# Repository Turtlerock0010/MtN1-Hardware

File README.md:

# MtN1-Hardware

> MtN1 Draft 1 3D Model, WIP

> [!IMPORTANT]
> [Check discussions and help out!!! 🥹](https://github.com/Turtlerock0010/MtN1-Hardware/discussions)

> [!NOTE]
> This is the hardware repository for the MtN1! For MtN1 software, go to [MtN1-Lib](https://github.com/Turtlerock0010/MtN1-Lib).

## About

### Q: What is this project?
A: The MtN1 (Motion-1) is a robotics motion expansion board designed to work with any microcontroller that supports QWIIC or I2C!

### Q: What is the goal of this project?
A: The goal of the MtN1 is to ensure complexity is a choice, not a compromise. Although simplicity and constraints allow for mechanisms that are designed with robustness, MtN1 is designed to allow for seasoned and rookie roboticists to truly expand on individual STEM efficacy.

### Q: What was the inspiration for this board?
A: Within MiniFRC -- an event hosted by The Terrorbytes [4561] -- I saw many very impressive creations, ranging from complete swerve drivetrains to advanced vision systems. But one common thread between them were the compromises made in order to work within the bounds of the most common robotics board used. Even I and the MiniFRC team I'm in (The Pink Fluffy Unicorns [83]) deliberated on how to distribute or simplify systems to fit these physical bounds!

### Q: Wait, no microcontroller onboard?
A: Yes!!! The MtN1 does not use a microcontroller. Instead, it uses a distributed control architecture to act as a primative version of one. This allows for cheaper costs, low latency control, universal I2C compatability, and 2 GPIO pin control!

### Q: Why the name MtN1 (Motion-1)?
A: I chose the name MtN1 as I felt like it was the name that properly describes the board's capabilities; and it looks stylish 😎.

## Non-Final Schematic

> MtN1 Draft 1 Schematic, WIP

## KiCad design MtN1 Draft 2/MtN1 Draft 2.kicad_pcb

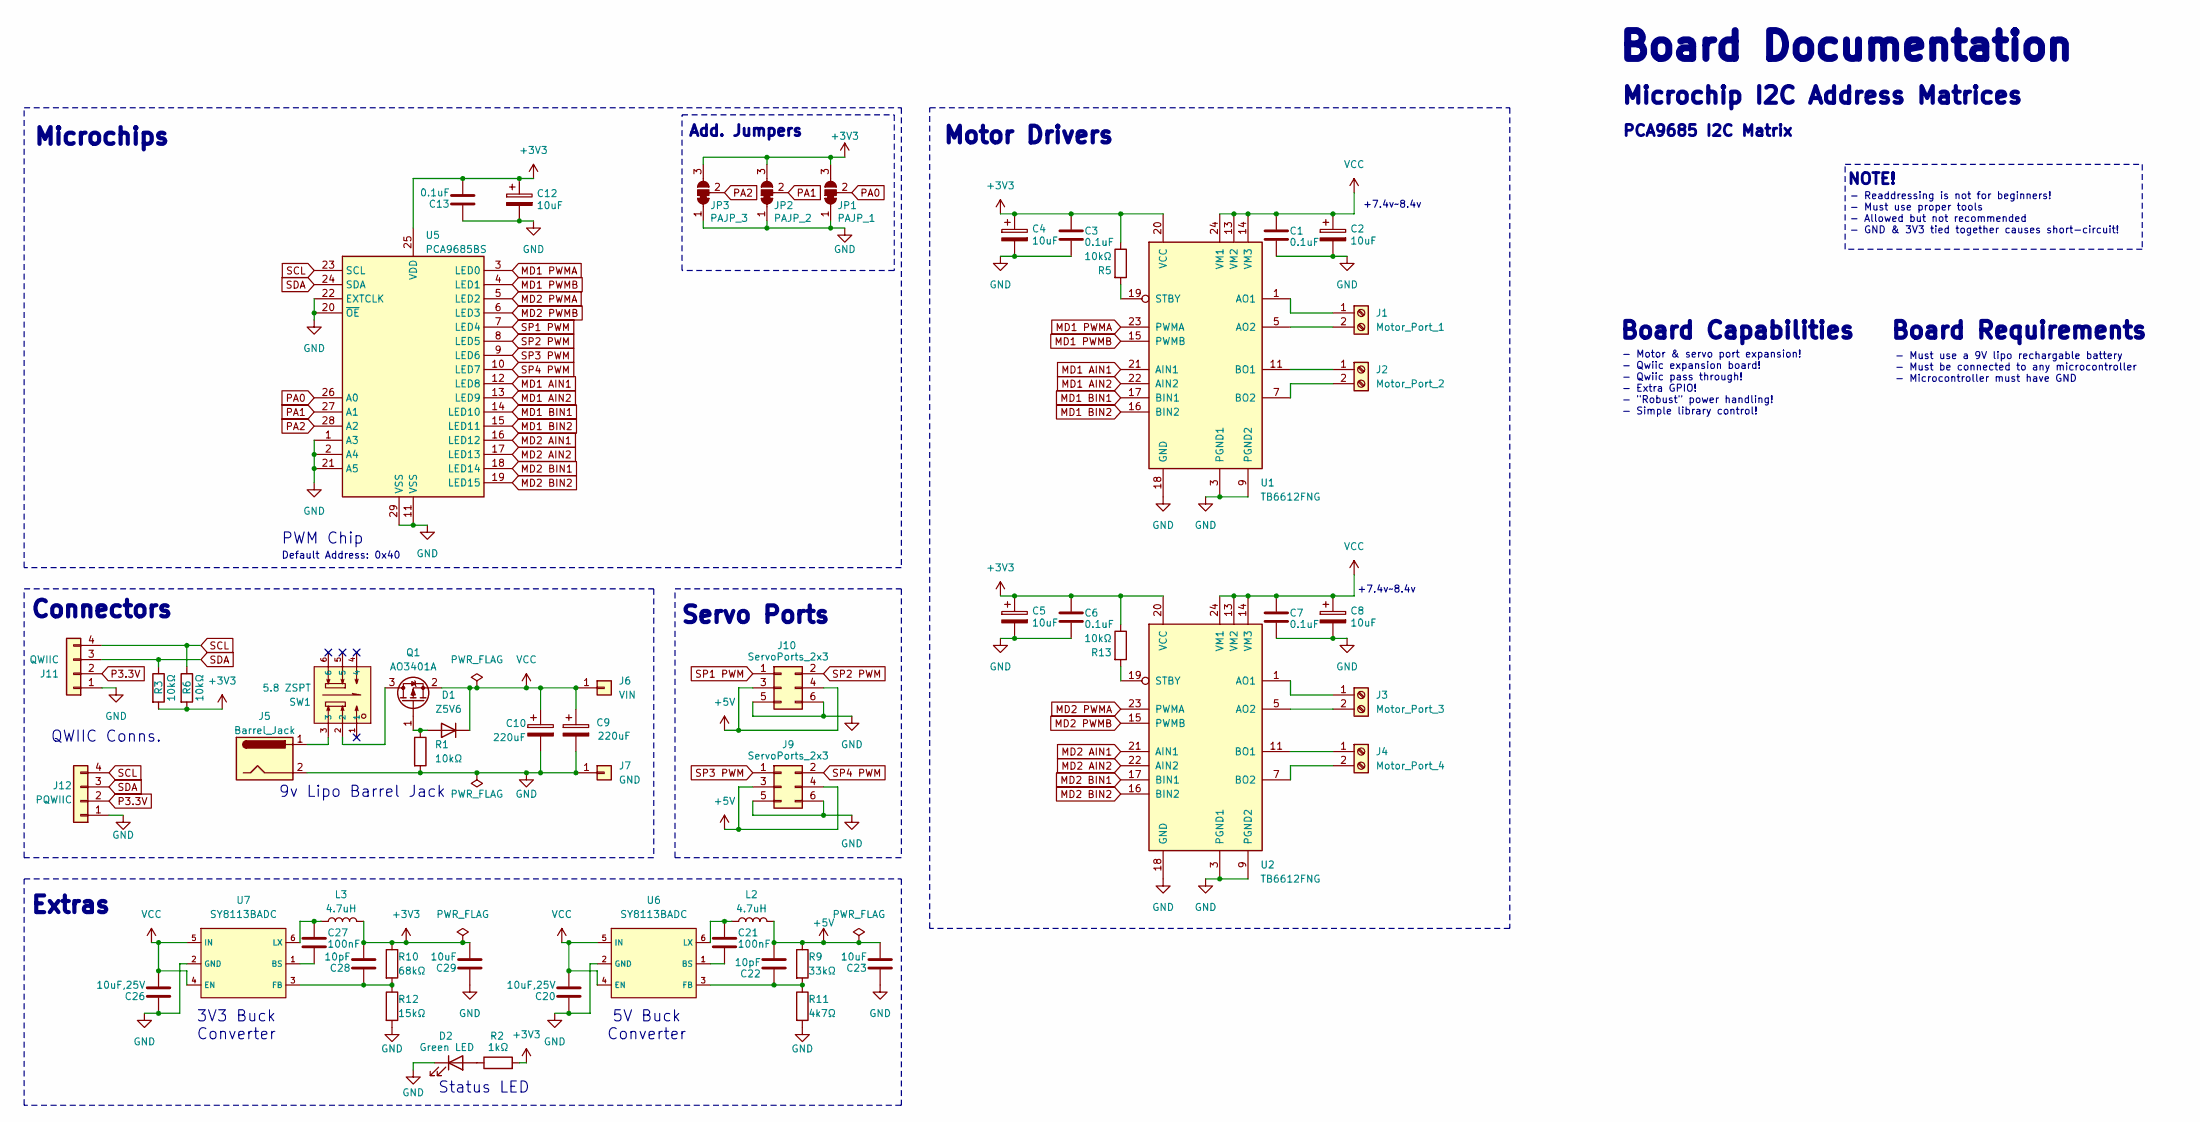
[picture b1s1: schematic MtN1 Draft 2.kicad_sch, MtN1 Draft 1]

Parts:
C1, C3, C6, C7, C13: 0.1uF; C_0402
C2, C4, C5, C8, C12: 10uF; C_0402
C9, C10: 220uF; CP_Elec_6.3x7.7
C20, C26: 10uF,25V; C_0603
C21, C27: 100nF; C_0402
C22, C28: 10pF; C_0402
C23, C29: 10uF; C_0603
D1: Z5V6; D_SOD-123
D2: Green LED; LED_0603_1608Metric
J1: Motor_Port_1; C8404_CONN-TH_WJ126V-5_0-2P
J2: Motor_Port_2; C8404_CONN-TH_WJ126V-5_0-2P
J3: Motor_Port_3; C8404_CONN-TH_WJ126V-5_0-2P
J4: Motor_Port_4; C8404_CONN-TH_WJ126V-5_0-2P
J5: Barrel_Jack; BarrelJack_Horizontal
J6: VIN; TestPoint_Pad_2.0x2.0mm
J7: GND; TestPoint_Pad_2.0x2.0mm
J9, J10: ServoPorts_2x3; PinHeader_2x03_P2.54mm_Vertical
J11: QWIIC; JST_SH_BM04B-SRSS-TB_1x04-1MP_P1.00mm_Vertical
J12: PQWIIC; JST_SH_BM04B-SRSS-TB_1x04-1MP_P1.00mm_Vertical
JP1: PAJP_1; SolderJumper-3_P1.3mm_Bridged12_RoundedPad1.0x1.5mm
JP2: PAJP_2; SolderJumper-3_P1.3mm_Bridged12_RoundedPad1.0x1.5mm
JP3: PAJP_3; SolderJumper-3_P1.3mm_Bridged12_RoundedPad1.0x1.5mm
L2, L3: 4.7uH; C98354_IND-SMD_L2_5-W2_0_WPN252012H
Q1: AO3401A; SOT-23
R1: 10kΩ; R_0603
R2: 1kΩ; R_0402
R3, R5, R6: 10kΩ; R_0402
R9: 33kΩ; R_0402
R10: 68kΩ; R_0402
R11: 4k7Ω; R_0402
R12: 15kΩ; R_0402
R13: 10kΩ; C25744_R0402
SW1: 5.8 ZSPT; C2681588_SW-TH_5_8ZSPT; LCSC C2681588
U1, U2: TB6612FNG; SSOP-24_5.3x8.2mm_P0.65mm
U5: PCA9685BS; QFN-28-1EP_6x6mm_P0.65mm_EP4.25x4.25mm
U6, U7: SY8113BADC; C78989_TSOT-23-6_L2_9-W1_6-P0_95-LS2_8-BR; LCSC C78989

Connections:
+3V3: C3.1, C4.1, C5.1, C6.1, C12.1, C13.2, C28.2, C29.2, JP1.3 (B), JP2.3 (B), JP3.3 (B), L3.2, R2.2, R3.2, R5.1, R6.2, R10.1, R13.1, U1.20 (VCC), U2.20 (VCC), U5.25 (VDD)
+5V: C22.2, C23.2, J9.3, J9.4, J10.3, J10.4, L2.2, R9.1
GND: C1.2, C2.2, C3.2, C4.2, C5.2, C6.2, C7.2, C8.2, C9.2, C10.2, C12.2, C13.1, C20.1, C23.1, C26.1, C29.1, D2.1 (K), J5.2, J7.1 (Pin_1_1), J9.5, J9.6, J10.5, J10.6, J11.1, J12.1, JP1.1 (A), JP2.1 (A), JP3.1 (A), R1.2, R11.2, R12.2, U1.3 (PGND1), U1.4 (PGND1), U1.9 (PGND2), U1.10 (PGND2), U1.18 (GND), U2.3 (PGND1), U2.4 (PGND1), U2.9 (PGND2), U2.10 (PGND2), U2.18 (GND), U5.1 (A3), U5.2 (A4), U5.11 (VSS), U5.20 (~OE), U5.21 (A5), U5.22 (EXTCLK), U5.29 (VSS), U6.2 (GND), U7.2 (GND)
MD1 AIN1: U1.21 (AIN1), U5.12 (LED8)
MD1 AIN2: U1.22 (AIN2), U5.13 (LED9)
MD1 BIN1: U1.17 (BIN1), U5.14 (LED10)
MD1 BIN2: U1.16 (BIN2), U5.15 (LED11)
MD1 PWMA: U1.23 (PWMA), U5.3 (LED0)
MD1 PWMB: U1.15 (PWMB), U5.4 (LED1)
MD2 AIN1: U2.21 (AIN1), U5.16 (LED12)
MD2 AIN2: U2.22 (AIN2), U5.17 (LED13)
MD2 BIN1: U2.17 (BIN1), U5.18 (LED14)
MD2 BIN2: U2.16 (BIN2), U5.19 (LED15)
MD2 PWMA: U2.23 (PWMA), U5.5 (LED2)
MD2 PWMB: U2.15 (PWMB), U5.6 (LED3)
unnamed: D1.2 (A), Q1.1 (G), R1.1
unnamed: D2.2 (A), R2.1
unnamed: J1.1, U1.1 (AO1), U1.2 (AO1)
unnamed: J1.2, U1.5 (AO2), U1.6 (AO2)
unnamed: J2.1, U1.11 (BO1), U1.12 (BO1)
unnamed: J2.2, U1.7 (BO2), U1.8 (BO2)
unnamed: J3.1, U2.1 (AO1), U2.2 (AO1)
unnamed: J3.2, U2.5 (AO2), U2.6 (AO2)
unnamed: J4.1, U2.11 (BO1), U2.12 (BO1)
unnamed: J4.2, U2.7 (BO2), U2.8 (BO2)
unnamed: J5.1, SW1.3
unnamed: Q1.3 (D), SW1.2
unnamed: R5.2, U1.19 (STBY)
unnamed: R13.2, U2.19 (STBY)
unnamed: C21.1, U6.1 (BS)
unnamed: C22.1, R9.2, R11.1, U6.3 (FB)
unnamed: C21.2, L2.1, U6.6 (LX)
unnamed: C27.1, U7.1 (BS)
unnamed: C28.1, R10.2, R12.1, U7.3 (FB)
unnamed: C27.2, L3.1, U7.6 (LX)
P3.3V: J11.2, J12.2
PA0: JP1.2 (C), U5.26 (A0)
PA1: JP2.2 (C), U5.27 (A1)
PA2: JP3.2 (C), U5.28 (A2)
SCL: J11.4, J12.4, R6.1, U5.23 (SCL)
SDA: J11.3, J12.3, R3.1, U5.24 (SDA)
SP1 PWM: J10.1, U5.7 (LED4)
SP2 PWM: J10.2, U5.8 (LED5)
SP3 PWM: J9.1, U5.9 (LED6)
SP4 PWM: J9.2, U5.10 (LED7)
VCC: C1.1, C2.1, C7.1, C8.1, C9.1, C10.1, C20.2, C26.2, D1.1 (K), J6.1 (Pin_1_1), Q1.2 (S), U1.13 (VM2), U1.14 (VM3), U1.24 (VM1), U2.13 (VM2), U2.14 (VM3), U2.24 (VM1), U6.4 (EN), U6.5 (IN), U7.4 (EN), U7.5 (IN)

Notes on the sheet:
QWIIC Conns.
Microchip I2C Address Matrices
3V3 Buck Converter
9v Lipo Barrel Jack
Status LED
5V Buck Converter
Default Address: 0x40
- Readdressing is not for beginners! - Must use proper tools - Allowed but not recommended - GND & 3V3 tied together causes short-circuit!
+7.4v~8.4v
Servo Ports
PWM Chip
- Motor & servo port expansion! - Qwiic expansion board! - Qwiic pass through! - Extra GPIO! - "Robust" power handling! - Simple library control!
PCA9685 I2C Matrix
Board Requirements
Microchips
NOTE!
Board Documentation
Connectors
- Must use a 9V lipo rechargable battery - Must be connected to any microcontroller - Microcontroller must have GND
Extras
Motor Drivers
Board Capabilities
Add. Jumpers

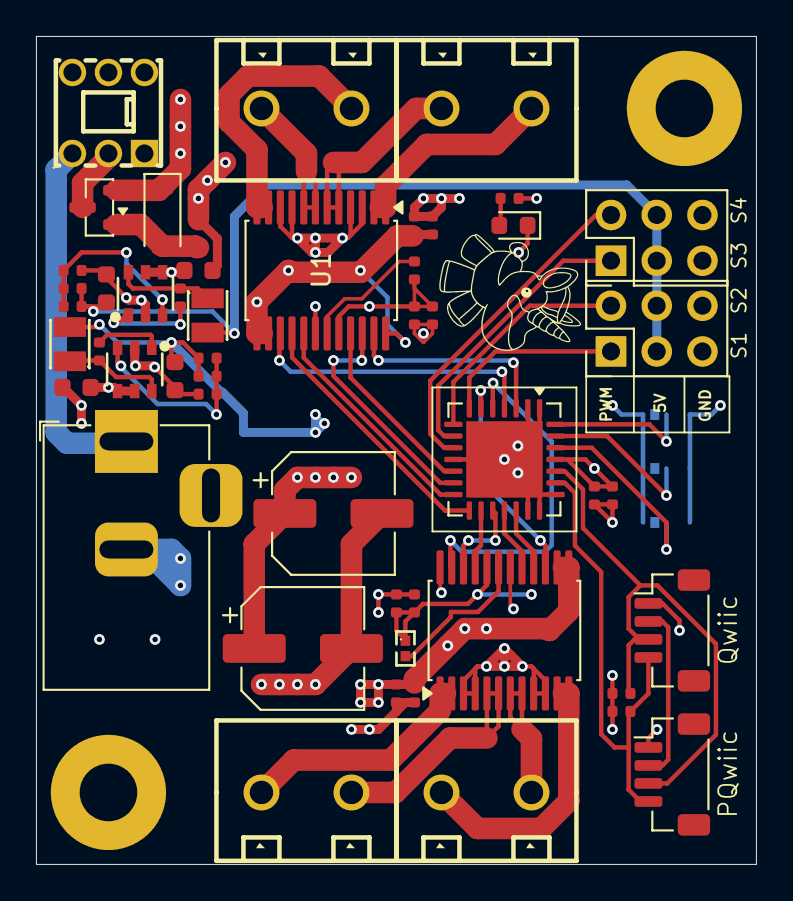
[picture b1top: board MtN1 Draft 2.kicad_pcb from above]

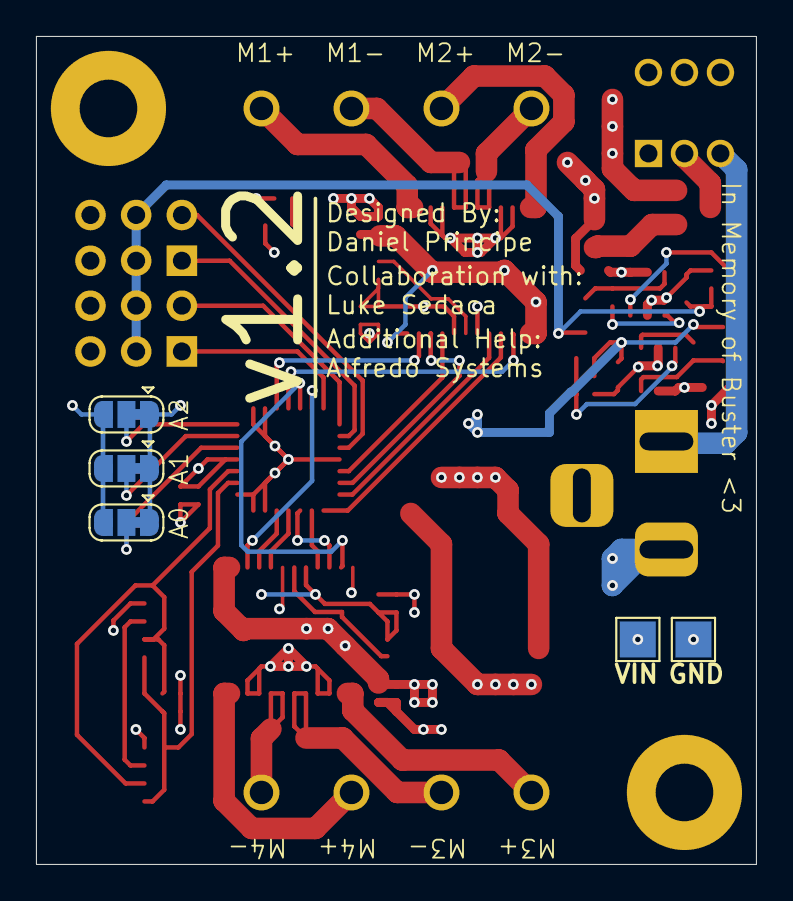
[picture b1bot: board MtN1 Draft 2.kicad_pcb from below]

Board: 4 copper layers, 40.0 x 46.0 mm, 55 parts (5 on the bottom side), 46 nets.

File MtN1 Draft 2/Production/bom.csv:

Designator,Footprint,Quantity,Value,LCSC Part #
"C1, C13, C3, C6, C7",C_0402,5,0.1uF,C141382
"C10, C9",CP_Elec_6.3x7.7,2,220uF,C4747974
"C12, C2, C4, C5, C8",C_0402,5,10uF,C15525
"C20, C26",C_0603,2,"10uF,25V",C96446
"C21, C27",C_0402,2,100nF,C1525
"C22, C28",C_0402,2,10pF,C32949
"C23, C29",C_0603,2,10uF,C19702
D1,D_SOD-123,1,Z5V6,C22612
D2,0603,1,Green LED,C122984
J1,C8404_CONN-TH_WJ126V-5_0-2P,1,Motor_Port_1,C8404
"J10, J9",PinHeader_2x03_P2.54mm_Vertical,2,ServoPorts_2x3,C5116479
J11,JST_SH_BM04B-SRSS-TB_1x04-1MP_P1.00mm_Vertical,1,QWIIC,C160390
J12,JST_SH_BM04B-SRSS-TB_1x04-1MP_P1.00mm_Vertical,1,PQWIIC,C160390
J2,C8404_CONN-TH_WJ126V-5_0-2P,1,Motor_Port_2,C8404
J3,C8404_CONN-TH_WJ126V-5_0-2P,1,Motor_Port_3,C8404
J4,C8404_CONN-TH_WJ126V-5_0-2P,1,Motor_Port_4,C8404
J5,BarrelJack_Horizontal,1,Barrel_Jack,C84007
J6,TestPoint_Pad_2.0x2.0mm,1,VIN,
J7,TestPoint_Pad_2.0x2.0mm,1,GND,
"L2, L3",C98354_IND-SMD_L2_5-W2_0_WPN252012H,2,4.7uH,C98354
Q1,SOT-23,1,AO3401A,C15127
R1,R_0603,1,10kΩ,C25804
R10,R_0402,1,68kΩ,C2909379
R11,R_0402,1,4k7Ω,C25900
R12,R_0402,1,15kΩ,C25756
R13,C25744_R0402,1,10kΩ,C25744
R2,R_0402,1,1kΩ,C11702
"R3, R5, R6",R_0402,3,10kΩ,C25744
R9,R_0402,1,33kΩ,C25779
SW1,C2681588_SW-TH_5_8ZSPT,1,5.8 ZSPT,C2681588
"U1, U2",SSOP-24_5.3x8.2mm_P0.65mm,2,TB6612FNG,C88224
U5,QFN-28-1EP_6x6mm_P0.65mm_EP4.25x4.25mm,1,PCA9685BS,C5191634
"U6, U7",C78989_TSOT-23-6_L2_9-W1_6-P0_95-LS2_8-BR,2,SY8113BADC,C78989

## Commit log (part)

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2026-05-11 Add CERN Open Hardware Licence v2
    Added CERN Open Hardware Licence Version 2 - Strongly Reciprocal to the project.
2026-05-11 Update README with project details and images
    Added project overview and goals for MtN1 hardware.
2026-05-11 Fix grammar and enhance FAQ clarity in README
    Corrected grammar and improved clarity in the FAQ section.
2026-05-15 Add discussions link to README
    Added a section for discussions and contributions.
2026-05-15 Update README section for discussions link
2026-05-15 Clarify project goal in README
    Updated the project goal description for clarity and detail.
2026-05-22 Update README with project details and images
2026-05-22 Updated project files up to Article 2
2026-05-22 Fix spelling errors in README.md
    Corrected spelling errors and improved clarity in the README.
2026-05-22 Update README to remove unnecessary note
    Removed note about useful information for users.
2026-05-22 Update README with important discussion link
2026-05-23 Updated project files up to Article 3
2026-05-23 Update README with MtN1 Draft 1 links and images
    Added links to MtN1 Draft 1 PDF files and updated schematic image.
2026-05-23 Remove duplicate PDF links from README
    Removed duplicate links to MtN1 Draft 1 PDF files.
2026-05-26 Update image in README.md
    Replaced old image with a new 3D model image.
2026-05-26 Update README with project details and links
    Added important notes and project description to README.
2026-05-26 Fix typo in README.md about hardware repository
2026-05-30 Add .gitignore to ignore local KiCad backups
    guys... its so much backups 😭
2026-05-30 Adding files for Article 5
    I can't do the article rn, but sometime later.
2026-05-30 Github Desktop stuff
2026-05-30 Add macOS system files to .gitignore
2026-05-30 Updated project files for Article 5
    Article 5 isn't done yet, but just updating files for the future when it is done.
2026-05-30 PCB layout cleanup
    I'm going to get absolutely obliterated the second I show this off 💔
2026-05-31 Trace cleanup; extra labels
    DRC likes me now 🎉, but probably not someone who understands electronics 😭
2026-06-12 Added Note To Silkscreen
